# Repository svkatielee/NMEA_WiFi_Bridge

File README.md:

View this project on [CADLAB.io](https://cadlab.io/node/916). 

# NMEA_WiFi_Bridge
An ESP8266-01 WiFi module to read NMEA serial data and UDP broadcast it to multiple openCPN instances as a Bridge.

<b>Update: This code has been tested with Arduino IDE rev 1.6.9 and ESP8266 addin of 2.1.0. Newer compilers fail.</b>

<b>Warning: A work in progress</b>

I want to be able to run openCPN on both a laptop and a tablet at the same time. I would like the laptop down below deck, safe from the rain and salt water spray. I would like to have a mostly waterproof tablet in the cockpit to monitor progress. And I would like to be able to quickly check the ship's status from the captain's berth when off watch, maybe on a smart phone.

The plan is to implement a device to read the serial data from all the boat instruments and send that data to openCPN over a WiFI link so there are no physical wires attached. It will broadcast the data with UDP so that multiple devices can read the data at the same time.

The ESP8266 ESP-01 was chosen because it was on hand and it has adequate I/O for this project.

The rs-232 input signal voltage should work with -12 to +12 volts. It was tested with a Garmin 72H which puts out -5 to +5.

<h3>Setup</h3>
Connect power and input signal rs-232 line with ground.
Press and hold config button, press reset, 
     continue to hold config until the LED stays lit.
Connect to the AP "NMEA WiFi Bridge" with a system/phone/etc.
Connect your brower to 10.1.1.1 with password in code "nmeawifi".`
Configure the form for your network and click the "configure" button.
Verify the results page.
Press reset or cycle power for the module to connect to your network.

To verify it is working, there is a status page on the address on the NMEA WiFi Bridge. Type this address into your browser.

<h3>Credits</h3>
The ESP was programmed with the Arduino IDE for ESP 1.6.5 and the board manager version 1.6.5-947-g39819f0.

Also uses the pfodWebWiFiConfig and adapted schematic from http://www.forward.com.au/pfod/CheapWifiShield/ESP2866_01_WiFi_Shield/ESP8266_01_WiFi_Shield_R1/index.html for the dynamic web config of the ESP.

I used the version 1.9 of the library pfodWifiConfig.zip which is now included as Doc/pfodWifiConfig.zip

<quote>
/**
 *  Cheap and Simple Wifi Shield for Arduino and other micros
 * http://www.forward.com.au/pfod/CheapWifiSheild/index.html
 *
 * (c)2015 Forward Computing and Control Pty. Ltd.
 * This code may be freely used for both private and commerical use.
 * Provide this copyright is maintained.
 */
</quote>

Follow his instructions for setting up the library from above. 
(Also copied here from http://www.forward.com.au/ for the verison I used)

---------------------------
<quote>
<h4>Programming the WiFi Shield</h4>

The WiFi Shield needs to be programmed once, only, and never again, with the web page configuration and the Serial to WiFi Bridge code.

To program the shield follow the instructions given on https://github.com/esp8266/Arduino under Installing With Boards Manager. When opening the Boards Manager from the Tools → Board menu and select Type Contributed and install the esp8266 platform. This project was compiled using the ESP8266 version 1.6.4-673-g8cd3697. Later versions well be better but may have their own bugs as the platform is evolving rapidly.

Close and re-open the Arduino IDE and you can now select “Generic ESP8266 Module” from Tools → Board menu.

You also need to install the latest version of pfodWifiConfig.zip which handles the storing and retrieval of the settings in EEPROM

a) Download this pfodWifiConfig.zip file to your computer, move it to your desktop or some other folder you can easily find<br>
b) Then use Arduino 1.6.5 IDE menu option Sketch → Import Library → Add Library to install it.<br>
(If Arduino does not let you install it because the library already exists then find and delete the older pfodWifiConfig folder and then import this one)<br>
c) Stop and restart the Arduino IDE and under File->Examples you should now see pfodWifiConfig.<br>
</quote>
---------------------------

Also borrowed from http://www.scienceprog.com/alternatives-of-max232-in-low-budget-projects/ for the rs-232 to ttl translation for the input pin.

And last but not least some programming concepts from https://github.com/wa0uwh/ERB-EspWebServer.

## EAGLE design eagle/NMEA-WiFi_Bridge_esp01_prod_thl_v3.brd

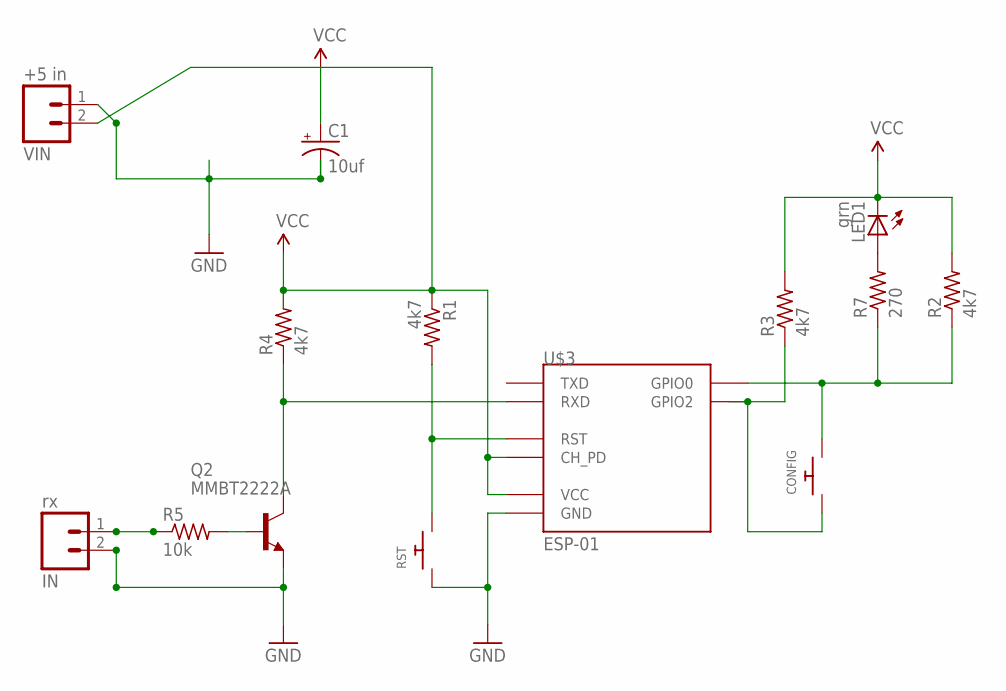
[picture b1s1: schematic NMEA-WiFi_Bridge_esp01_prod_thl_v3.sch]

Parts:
C1: 10uf; E2,5-6
CONFIG: SWITCH_PUSHBUTTONEVQ-PE; TACT_PANA-EVQ
IN: rx; MOLEX-1X2
LED1: grn; LED3MM
Q2: MMBT2222A; TO92-CBE
R1: 4k7; 0207/2V
R2, R3: 4k7; 0207/7
R4: 4k7; 0207/5V
R5: 10k; 0207/2V
R7: 270; 0207/7
RST: SWITCH_PUSHBUTTONEVQ-PE; TACT_PANA-EVQ
U$3: ESP-01
VIN: +5 in; MOLEX-1X2

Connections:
GND: C1.-, IN.2, Q2.E, RST.P$1, U$3.GND, VIN.1
GPIO0: CONFIG.P$2, R2.1, R7.1, U$3.GPIO0
unnamed: CONFIG.P$1, R3.1, U$3.GPIO2
unnamed: Q2.B, R5.2
unnamed: IN.1, R5.1
unnamed: LED1.A, R7.2
RST: R1.2, RST.P$2, U$3.RST
RX: Q2.C, R4.1, U$3.RX (RXD)
VCC: C1.+, LED1.K (C), R1.1, R2.2, R3.2, R4.2, U$3.CH_PD, U$3.VCC, VIN.2

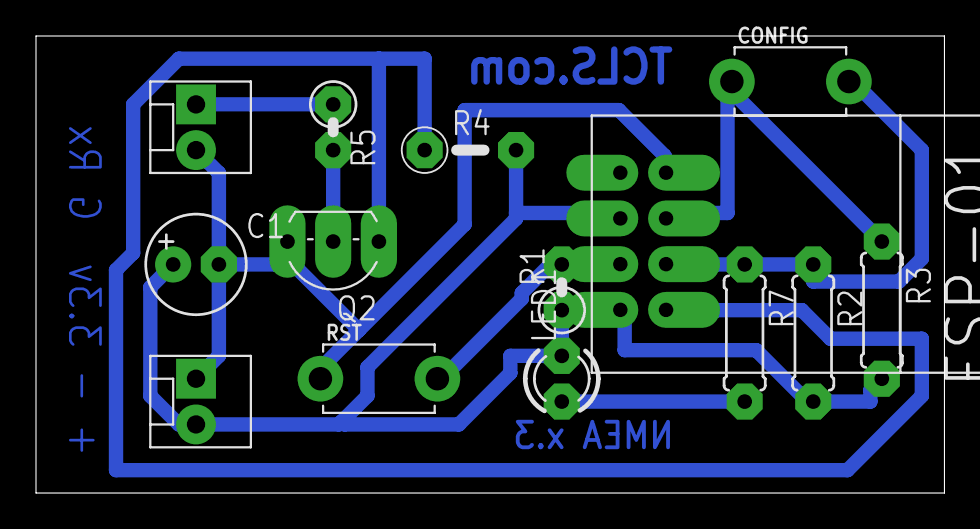
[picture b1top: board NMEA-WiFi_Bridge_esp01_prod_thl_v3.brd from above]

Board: 2 copper layers, 50.5 x 25.4 mm, 14 parts (0 on the bottom side), 9 nets.

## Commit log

2015-09-13 Rev LGL.00.04 initial commit
2015-09-14 Rev LGL.00.05 name change, update readme
2015-09-18 Add GPL v2 license
2015-10-18 Add blink LED while connecting to SSID
2015-12-25 Update README.md
    added note about pfodWifiConfig.h library
2016-01-14 Added ver 1.9 of pfodWiFiConfig.zip and instructions
2016-03-18 add eagle files sch brd version 0.3
2016-03-18 add eagle files sch brd version 0.3 and png
2016-06-27 fixed const char* error
2016-07-13 Update README for revisions of tools that are OK
2018-04-21 Backlink to CADLAB.io has been added.

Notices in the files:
parts and their libraries:
SparkFun-Connectors: Licensing: Creative Commons ShareAlike 4.0 International - https://creativecommons.org/licenses/by-sa/4.0
